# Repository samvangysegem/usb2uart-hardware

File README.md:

# USB2UART

USB-C to four UART ports, based on the CH344Q and designed in KiCad.

- `usb2uart-kicad/` — KiCad schematic and PCB. Open `usb2uart-kicad.kicad_pro` to get started.
- `manufacturing/` — Gerbers, drill files, BOM, and component placement CSV for JLCPCB.
- `docs/` — Reference documentation.

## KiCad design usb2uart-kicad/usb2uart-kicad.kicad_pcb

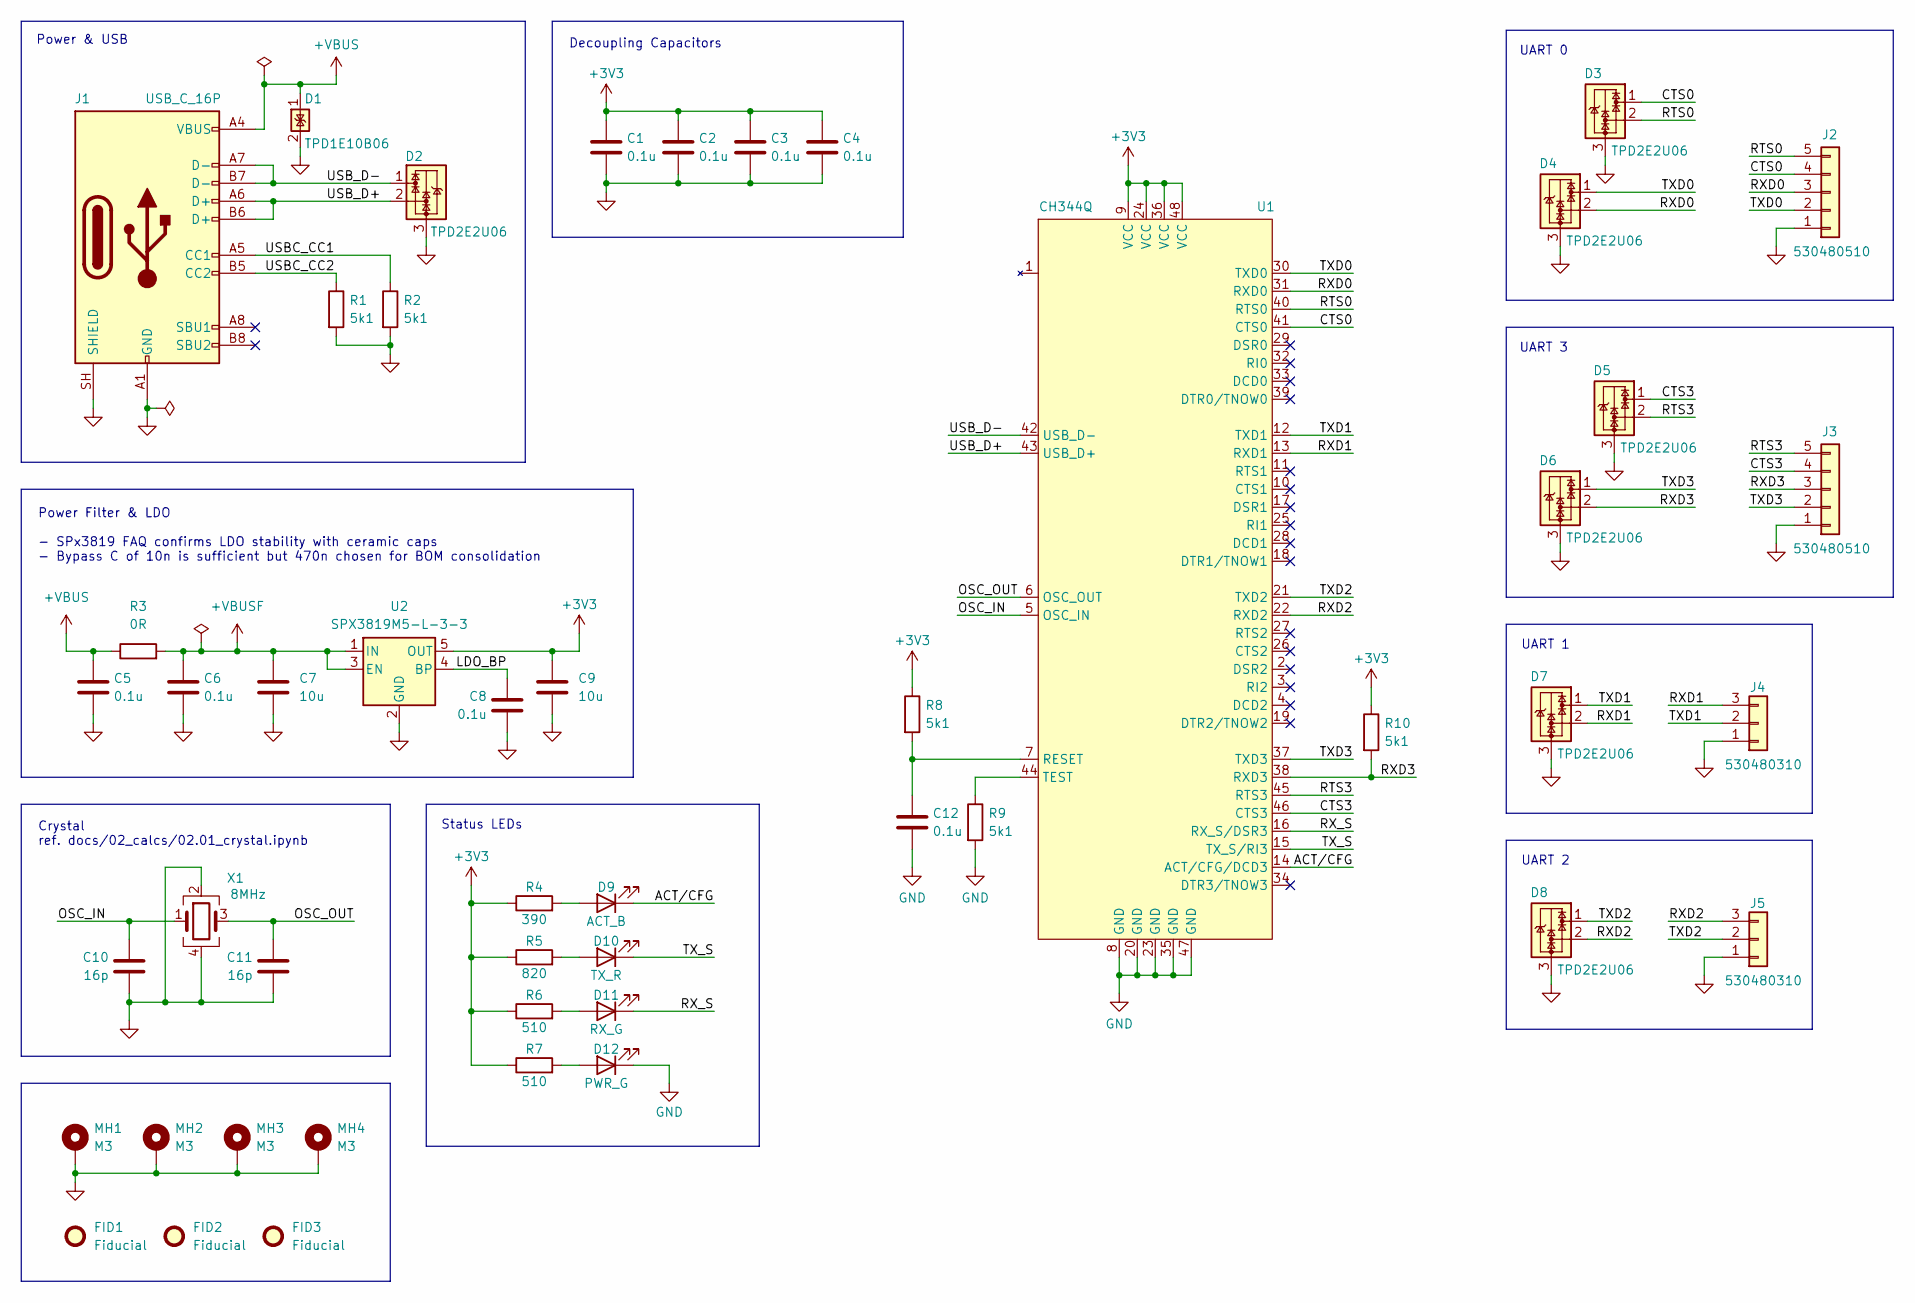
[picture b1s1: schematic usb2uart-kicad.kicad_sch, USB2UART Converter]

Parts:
C1, C2, C3, C4, C5, C6, C8, C12: 0.1u; C_0402_1005Metric; MPN CL05B104KO5NNNC; LCSC Part # C1525
C7: 10u; C_0805_2012Metric_Pad1.18x1.45mm_HandSolder; MPN CL21A106KAYNNNE; LCSC Part # C15850
C9: 10u; C_0805_2012Metric; MPN CL21A106KAYNNNE; LCSC Part # C15850
C10, C11: 16p; C_0402_1005Metric; MPN 0402CG150J500NT; LCSC Part # C1548
D1: TPD1E10B06; Texas_DPY0002A_0.6x1mm_P0.65mm; MPN TPD1E10B06DPYR; LCSC Part # C48260
D2, D3, D4, D5, D6, D7, D8: TPD2E2U06; SOT-323_SC-70; MPN TPD2E2U06QDCKRQ1; LCSC Part # C915089
D9: ACT_B; LED_0603_1608Metric; MPN KT-0603B; LCSC Part # C2288
D10: TX_R; LED_0603_1608Metric; MPN KT-0603R; LCSC Part # C2286
D11: RX_G; LED_0603_1608Metric; MPN KT-0603G; LCSC Part # C12624
D12: PWR_G; LED_0603_1608Metric; MPN KT-0603G; LCSC Part # C12624
FID1, FID2, FID3: Fiducial; Fiducial_1mm_Mask2mm
J1: USB_C_16P; USB_C_Receptacle_GCT_USB4105-xx-A_16P_TopMnt_Horizontal; MPN TYPE-C 16PIN 2MD(073); LCSC Part # C2765186
J2, J3: 530480510; Molex_PicoBlade_53048-0510_1x05_P1.25mm_Horizontal; MPN 530480510; LCSC Part # C588276
J4, J5: 530480310; Molex_PicoBlade_53048-0310_1x03_P1.25mm_Horizontal; MPN 530480310; LCSC Part # C505275
MH1, MH2, MH3, MH4: M3; MountingHole_3.2mm_M3_Pad_Via
R1, R2, R8, R9, R10: 5k1; R_0402_1005Metric; MPN 0402WGF5101TCE; LCSC Part # C25905
R3: 0R; R_0805_2012Metric_Pad1.20x1.40mm_HandSolder; MPN 0805W8F0000T5E; LCSC Part # C17477
R4: 390; R_0603_1608Metric_Pad0.98x0.95mm_HandSolder; MPN 0603WAF3900T5E; LCSC Part # C23151
R5: 820; R_0603_1608Metric_Pad0.98x0.95mm_HandSolder; MPN 0603WAF8200T5E; LCSC Part # C23253
R6, R7: 510; R_0603_1608Metric_Pad0.98x0.95mm_HandSolder; MPN 0603WAF5100T5E; LCSC Part # C23193
U1: CH344Q; LQFP-48_7x7mm_P0.5mm; MPN CH344Q; LCSC Part # C2988084
U2: SPX3819M5-L-3-3; SOT-23-5; MPN SPX3819M5-L-3-3/TR; LCSC Part # C9055
X1: 8MHz; Crystal_SMD_3225-4Pin_3.2x2.5mm; MPN X32258MOB4SI; LCSC Part # C2682775

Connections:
+3V3: C1.1, C2.1, C3.1, C4.1, C9.1, R4.1, R5.1, R6.1, R7.1, R8.1, R10.1, U1.9 (VCC), U1.24 (VCC), U1.36 (VCC), U1.48 (VCC), U2.5 (OUT)
+VBUS: C5.1, D1.1, J1.A4 (VBUS), J1.A9 (VBUS), J1.B4 (VBUS), J1.B9 (VBUS), R3.1
+VBUSF: C6.1, C7.1, R3.2, U2.1 (IN), U2.3 (EN)
/ACT/CFG: D9.1 (K), U1.14 (ACT/CFG/DCD3)
/CTS0: D3.1, J2.4, U1.41 (CTS0)
/CTS3: D5.1, J3.4, U1.46 (CTS3)
/LDO_BP: C8.1, U2.4 (BP)
/OSC_IN: C10.1, U1.5 (OSC_IN), X1.1
/OSC_OUT: C11.1, U1.6 (OSC_OUT), X1.3
/RTS0: D3.2, J2.5, U1.40 (RTS0)
/RTS3: D5.2, J3.5, U1.45 (RTS3)
/RXD0: D4.2, J2.3, U1.31 (RXD0)
/RXD1: D7.2, J4.3, U1.13 (RXD1)
/RXD2: D8.2, J5.3, U1.22 (RXD2)
/RXD3: D6.2, J3.3, R10.2, U1.38 (RXD3)
/RX_S: D11.1 (K), U1.16 (RX_S/DSR3)
/TXD0: D4.1, J2.2, U1.30 (TXD0)
/TXD1: D7.1, J4.2, U1.12 (TXD1)
/TXD2: D8.1, J5.2, U1.21 (TXD2)
/TXD3: D6.1, J3.2, U1.37 (TXD3)
/TX_S: D10.1 (K), U1.15 (TX_S/RI3)
/USBC_CC1: J1.A5 (CC1), R2.1
/USBC_CC2: J1.B5 (CC2), R1.1
/USB_D+: D2.2, J1.A6 (D+), J1.B6 (D+), U1.43 (USB_D+)
/USB_D-: D2.1, J1.A7 (D-), J1.B7 (D-), U1.42 (USB_D-)
GND: C1.2, C2.2, C3.2, C4.2, C5.2, C6.2, C7.2, C8.2, C9.2, C10.2, C11.2, C12.2, D1.2, D2.3, D3.3, D4.3, D5.3, D6.3, D7.3, D8.3, D12.1 (K), J1.A1 (GND), J1.A12 (GND), J1.B1 (GND), J1.B12 (GND), J1.SH (SHIELD), J2.1, J3.1, J4.1, J5.1, MH1.1 (1_1), MH2.1 (1_1), MH3.1 (1_1), MH4.1 (1_1), R1.2, R2.2, R9.2, U1.8 (GND), U1.20 (GND), U1.23 (GND), U1.35 (GND), U1.47 (GND), U2.2 (GND), X1.2, X1.4
unnamed: D9.2 (A), R4.2
unnamed: D10.2 (A), R5.2
unnamed: D11.2 (A), R6.2
unnamed: D12.2 (A), R7.2
unnamed: C12.1, R8.2, U1.7 (RESET)
unnamed: R9.1, U1.44 (TEST)

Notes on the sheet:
Crystal ref. docs/02_calcs/02.01_crystal.ipynb
Power Filter & LDO - SPx3819 FAQ confirms LDO stability with ceramic caps - Bypass C of 10n is sufficient but 470n chosen for BOM consolidation
UART 2
UART 1
UART 3
Status LEDs
Power & USB
UART 0
Decoupling Capacitors

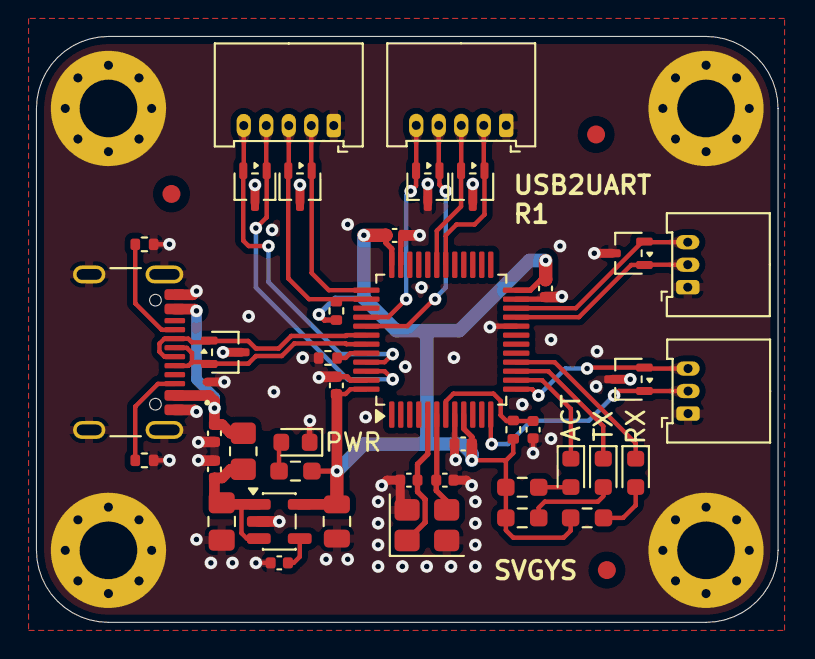
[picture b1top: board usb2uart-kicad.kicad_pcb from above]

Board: 4 copper layers, 41.2 x 32.5 mm, 49 parts (0 on the bottom side), 32 nets.
